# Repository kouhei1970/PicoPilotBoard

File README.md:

# PicoPilotBoard
Flight Conttoller board data for KiCAD

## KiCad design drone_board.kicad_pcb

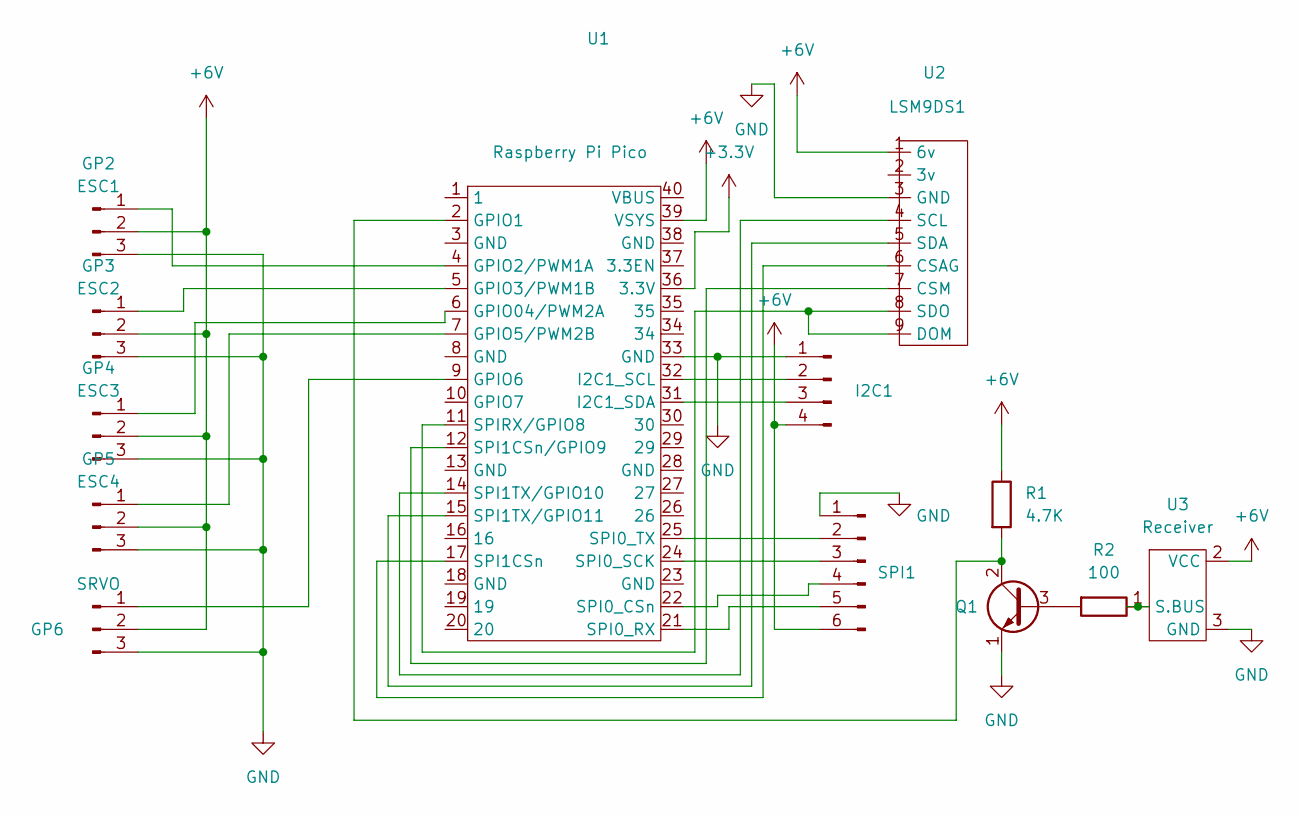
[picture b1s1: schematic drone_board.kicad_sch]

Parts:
GP2: ESC1; PinHeader_1x03_P2.54mm_Vertical
GP3: ESC2; PinHeader_1x03_P2.54mm_Vertical
GP4: ESC3; PinHeader_1x03_P2.54mm_Vertical
GP5: ESC4; PinHeader_1x03_P2.54mm_Vertical
GP6: SRVO; PinHeader_1x03_P2.54mm_Vertical
I2C1: Conn_01x04_Male; PinHeader_1x04_P2.54mm_Vertical
Q1: Q_NPN_CBE; TO-92L_Inline
R1: 4.7K; R_Axial_DIN0207_L6.3mm_D2.5mm_P10.16mm_Horizontal
R2: 100; R_Axial_DIN0207_L6.3mm_D2.5mm_P10.16mm_Horizontal
SPI1: Conn_01x06_Male; PinHeader_1x06_P2.54mm_Vertical
U1: Raspberry Pi Pico; Raspberry_Pi_Pico
U2: LSM9DS1
U3: Receiver

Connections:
+3V3: U1.36 (3.3V)
+6V: GP2.2, GP3.2, GP4.2, GP5.2, GP6.2, I2C1.4, R1.1, SPI1.6, U1.39 (VSYS), U2.1 (6v), U3.2 (VCC)
GND: GP2.3, GP3.3, GP4.3, GP5.3, GP6.3, I2C1.1, Q1.1 (E), SPI1.1, U1.33 (GND), U2.3 (GND), U3.3 (GND)
unnamed: GP2.1, U1.4 (GPIO2/PWM1A)
unnamed: GP3.1, U1.5 (GPIO3/PWM1B)
unnamed: GP4.1, U1.6 (GPIO04/PWM2A)
unnamed: GP5.1, U1.7 (GPIO5/PWM2B)
unnamed: GP6.1, U1.9 (GPIO6)
unnamed: I2C1.2, U1.32 (I2C1_SCL)
unnamed: I2C1.3, U1.31 (I2C1_SDA)
unnamed: Q1.2 (C), R1.2, U1.2 (GPIO1)
unnamed: Q1.3 (B), R2.2
unnamed: R2.1, U3.1 (S.BUS)
unnamed: SPI1.2, U1.25 (SPI0_TX)
unnamed: SPI1.3, U1.24 (SPI0_SCK)
unnamed: SPI1.4, U1.22 (SPI0_CSn)
unnamed: SPI1.5, U1.21 (SPI0_RX)
unnamed: U1.12 (SPI1CSn/GPIO9), U2.7 (CSM)
unnamed: U1.14 (SPI1TX/GPIO10), U2.4 (SCL)
unnamed: U1.15 (SPI1TX/GPIO11), U2.5 (SDA)
unnamed: U1.17 (SPI1CSn), U2.6 (CSAG)
unnamed: U1.11 (SPIRX/GPIO8), U2.8 (SDO), U2.9 (DOM)

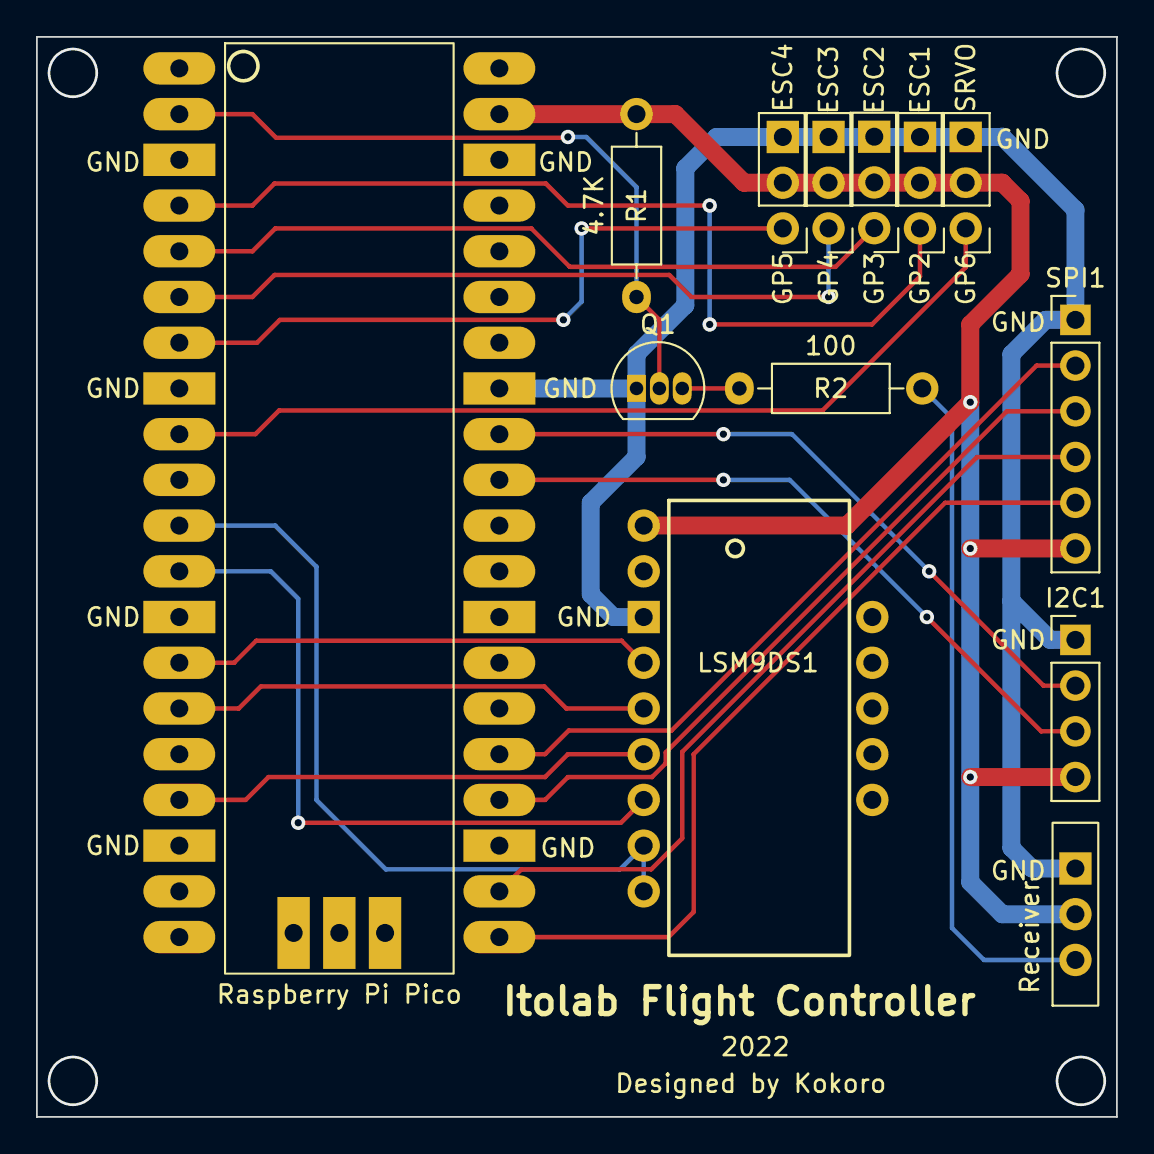
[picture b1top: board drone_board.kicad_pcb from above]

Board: 2 copper layers, 60.0 x 60.0 mm, 13 parts (0 on the bottom side), 21 nets.
